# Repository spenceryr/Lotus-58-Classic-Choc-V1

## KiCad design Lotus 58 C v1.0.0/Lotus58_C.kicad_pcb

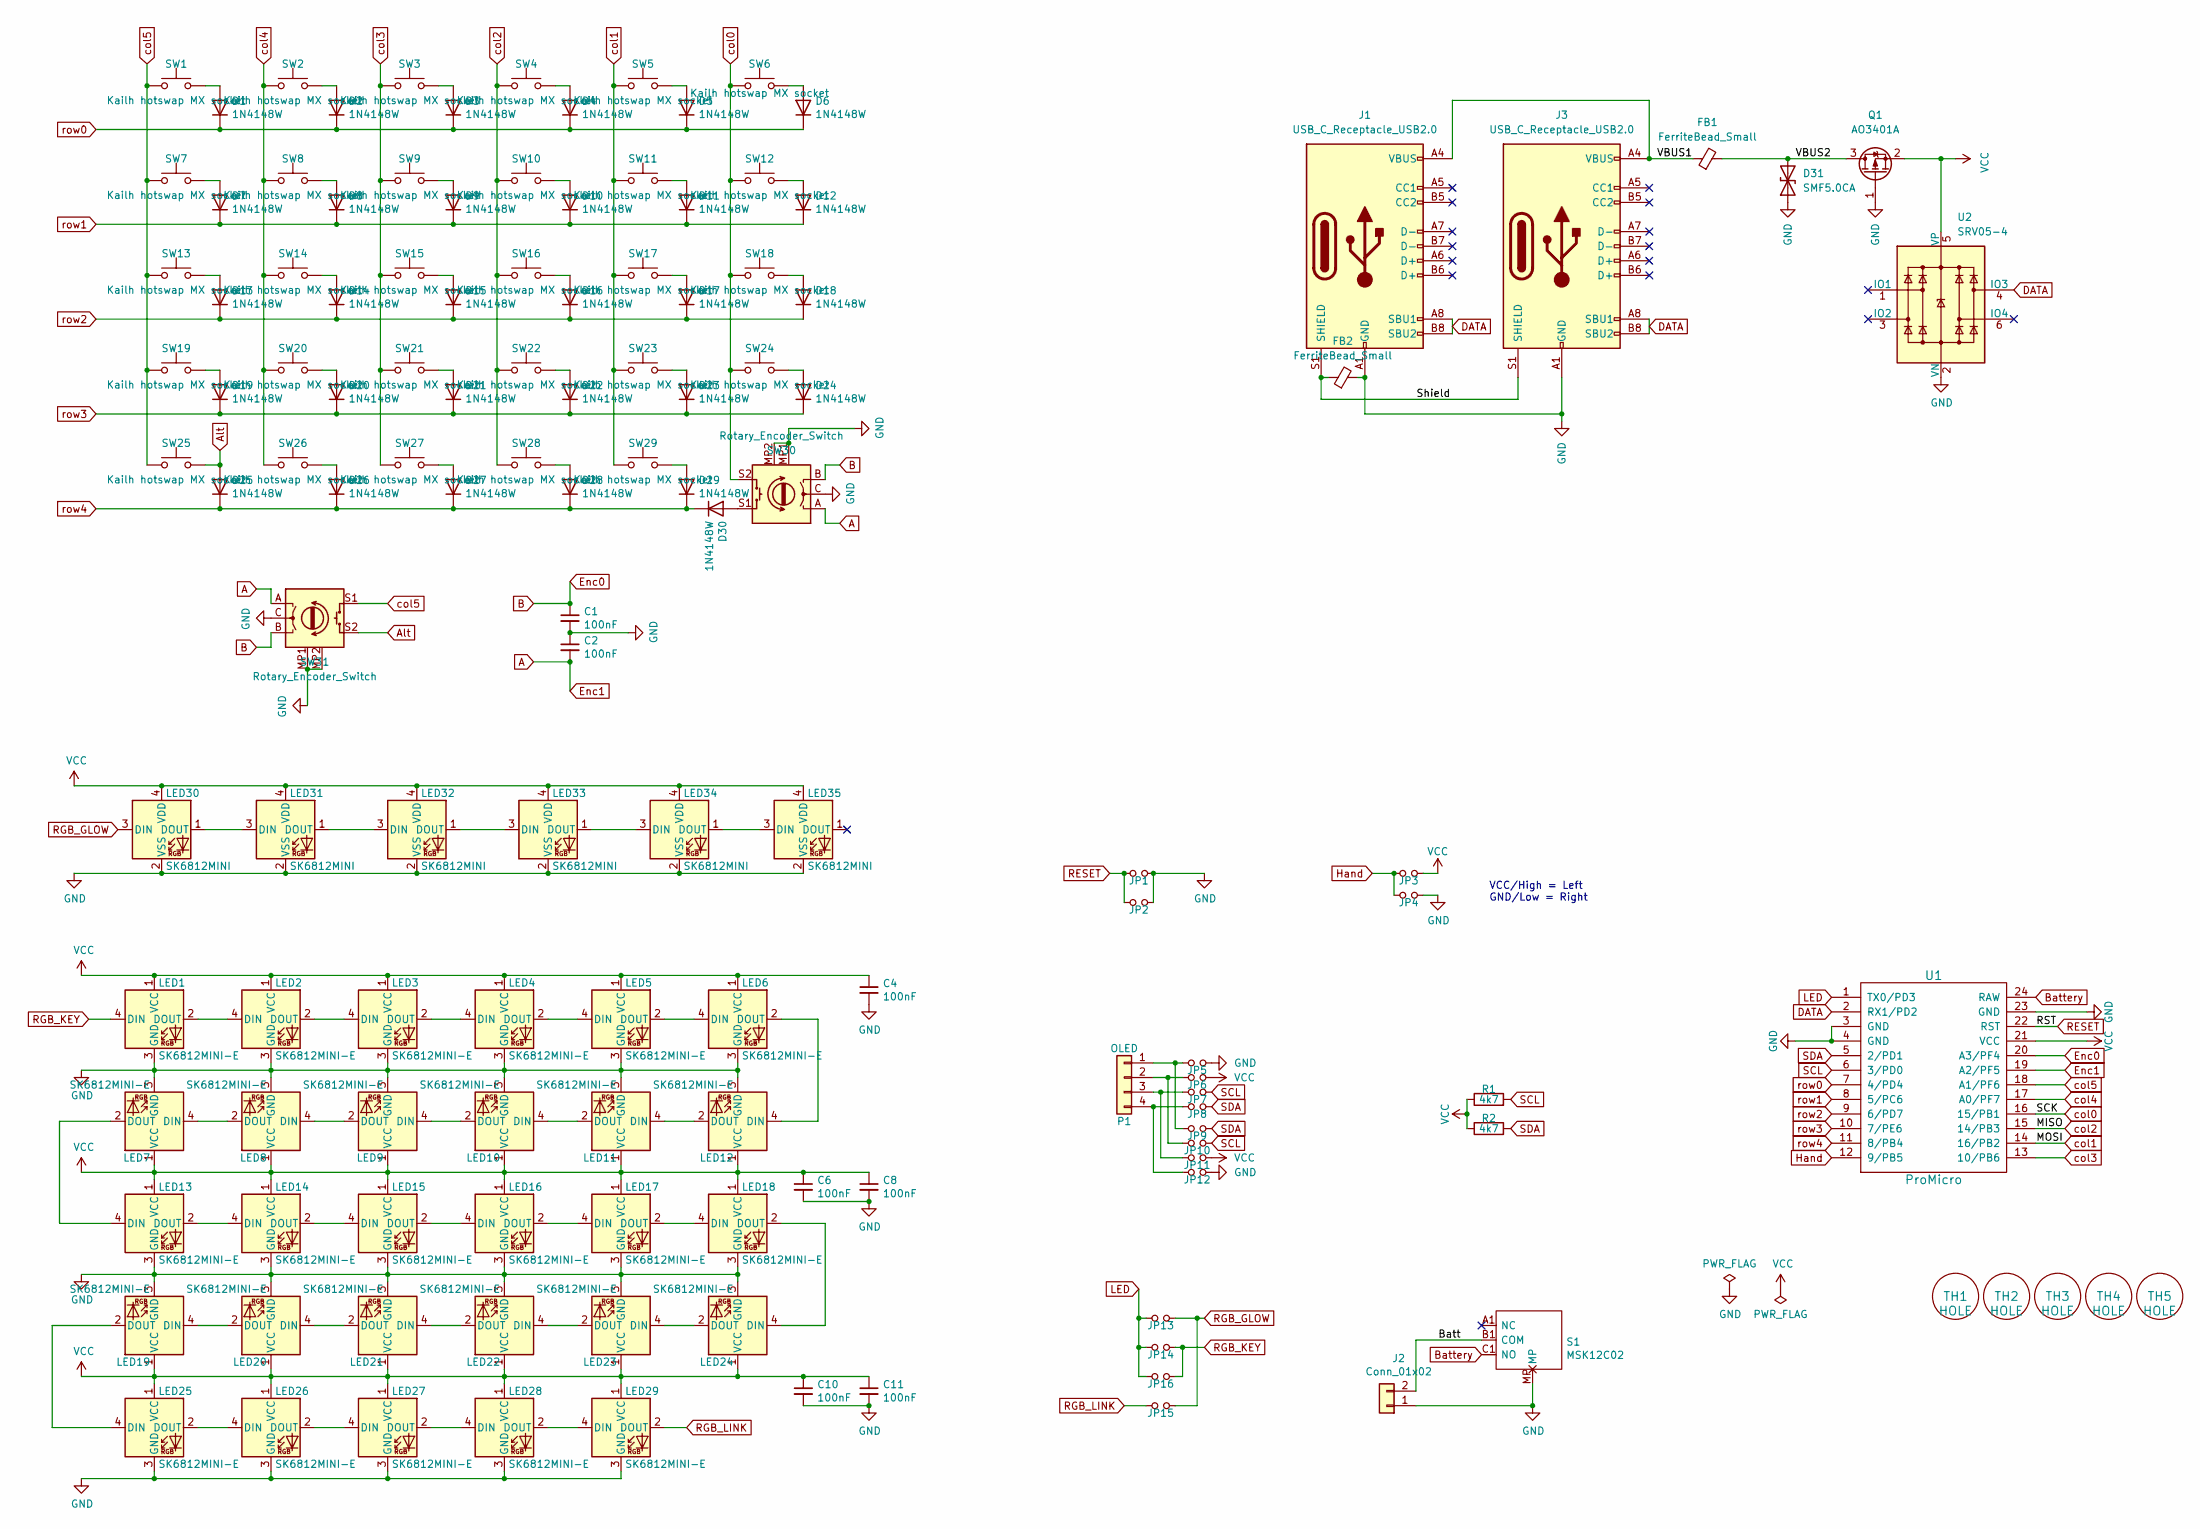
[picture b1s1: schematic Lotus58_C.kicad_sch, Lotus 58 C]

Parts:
C1, C2, C4, C6, C8, C10, C11: 100nF; C_0603_1608Metric_Pad1.08x0.95mm_HandSolder
D1, D2, D3, D4, D5, D6, D7, D8, D9, D10, D11, D12, D13, D14, D15, D16, D17, D18, D19, D20, D21, D22, D23, D24, D25, D26, D27, D28, D29, D30: 1N4148W; D_SOD-123
D31: SMF5.0CA; D_SOD-123
FB1, FB2: FerriteBead_Small; C_0805_2012Metric_Pad1.18x1.45mm_HandSolder
J1, J3: USB_C_Receptacle_USB2.0; HRO_TYPE-C-31-M-12
J2: Conn_01x02; PinHeader_1x02_P2.54mm_Vertical
JP1, JP2: RESET; Jumper_Mini
JP3: LEFT; Jumper_Mini
JP4: RIGHT; Jumper_Mini
JP5, JP6, JP7, JP8, JP9, JP10, JP11, JP12: Jumper_NO_Small; Jumper_Mini
JP13, JP14, JP15, JP16: FULL; Jumper_Mini
LED1, LED2, LED3, LED4, LED5, LED6, LED7, LED8, LED9, LED10, LED11, LED12, LED13, LED14, LED15, LED16, LED17, LED18, LED19, LED20, LED21, LED22, LED23, LED24, LED25, LED26, LED27, LED28, LED29: SK6812MINI-E; MX_SK6812MINI-E_REVERSIBLE
LED30, LED31, LED32, LED33, LED34, LED35: SK6812MINI; LED_SK6812MINI_PLCC4_3.5x3.5mm_P1.75mm
P1: OLED; SSD1306-0.91-OLED-4pin-128x32
Q1: AO3401A; SOT-23
R1, R2: 4k7; R_0603_1608Metric_Pad0.98x0.95mm_HandSolder
S1: MSK12C02; Manufacturer_Part_Number MSK12C02
SW1, SW2, SW3, SW4, SW5, SW6, SW7, SW8, SW9, SW10, SW11, SW12, SW13, SW14, SW15, SW16, SW17, SW18, SW19, SW20, SW21, SW22, SW23, SW24, SW25, SW26, SW27, SW28, SW29: Kailh hotswap MX socket; Kailh_socket_MX_reversible_RGB
SW30: Rotary_Encoder_Switch; RotaryEncoder_Alps_EC11E-Switch_Vertical_H20_special
SW31: Rotary_Encoder_Switch; RotaryEncoder_Alps_EC11E-Switch_Special
TH1, TH2, TH3, TH4, TH5: HOLE; MountingHole_3.7mm
U1: ProMicro; ProMicro_Reversible
U2: SRV05-4; SOT-23-6

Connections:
/Batt: J2.2, S1.B1 (COM)
/Shield: FB2.1, J1.S1 (SHIELD), J3.S1 (SHIELD)
/VBUS1: FB1.1, J1.A4 (VBUS), J1.A9 (VBUS), J1.B4 (VBUS), J1.B9 (VBUS), J3.A4 (VBUS), J3.A9 (VBUS), J3.B4 (VBUS), J3.B9 (VBUS)
/VBUS2: D31.2 (A2), FB1.2, Q1.3 (D)
A: C2.2, SW30.A, SW31.A, U1.19 (A2/PF5)
Alt: D25.2 (A), SW25.2, SW31.S2
B: C1.1, SW30.B, SW31.B, U1.20 (A3/PF4)
Battery: S1.C1 (NO), U1.24 (RAW)
DATA: J1.A8 (SBU1), J1.B8 (SBU2), J3.A8 (SBU1), J3.B8 (SBU2), U1.2 (RX1/PD2), U2.4 (IO3)
GND: C1.2, C2.1, C4.2, C6.2, C8.2, C10.2, C11.2, D31.1 (A1), FB2.2, J1.A1 (GND), J1.A12 (GND), J1.B1 (GND), J1.B12 (GND), J2.1, J3.A1 (GND), J3.A12 (GND), J3.B1 (GND), J3.B12 (GND), JP1.2, JP2.2, JP4.2, JP5.2, JP12.2, LED1.3 (GND), LED2.3 (GND), LED3.3 (GND), LED4.3 (GND), LED5.3 (GND), LED6.3 (GND), LED7.3 (GND), LED8.3 (GND), LED9.3 (GND), LED10.3 (GND), LED11.3 (GND), LED12.3 (GND), LED13.3 (GND), LED14.3 (GND), LED15.3 (GND), LED16.3 (GND), LED17.3 (GND), LED18.3 (GND), LED19.3 (GND), LED20.3 (GND), LED21.3 (GND), LED22.3 (GND), LED23.3 (GND), LED24.3 (GND), LED25.3 (GND), LED26.3 (GND), LED27.3 (GND), LED28.3 (GND), LED29.3 (GND), LED30.2 (VSS), LED31.2 (VSS), LED32.2 (VSS), LED33.2 (VSS), LED34.2 (VSS), LED35.2 (VSS), Q1.1 (G), S1.MP, SW30.C, SW30.MP1 (GND), SW30.MP2 (GND), SW31.C, SW31.MP1 (GND), SW31.MP2 (GND), U1.3 (GND), U1.4 (GND), U1.23 (GND), U2.2 (VN)
Hand: JP3.1, JP4.1, U1.12 (9/PB5)
LED: JP13.1, JP14.1, JP16.1, U1.1 (TX0/PD3)
unnamed: D1.2 (A), SW1.2
unnamed: D2.2 (A), SW2.2
unnamed: D3.2 (A), SW3.2
unnamed: D4.2 (A), SW4.2
unnamed: D5.2 (A), SW5.2
unnamed: D6.2 (A), SW6.2
unnamed: D7.2 (A), SW7.2
unnamed: D8.2 (A), SW8.2
unnamed: D9.2 (A), SW9.2
unnamed: D10.2 (A), SW10.2
unnamed: D11.2 (A), SW11.2
unnamed: D12.2 (A), SW12.2
unnamed: D13.2 (A), SW13.2
unnamed: D14.2 (A), SW14.2
unnamed: D15.2 (A), SW15.2
unnamed: D16.2 (A), SW16.2
unnamed: D17.2 (A), SW17.2
unnamed: D18.2 (A), SW18.2
unnamed: D19.2 (A), SW19.2
unnamed: D20.2 (A), SW20.2
unnamed: D21.2 (A), SW21.2
unnamed: D22.2 (A), SW22.2
unnamed: D23.2 (A), SW23.2
unnamed: D24.2 (A), SW24.2
unnamed: D26.2 (A), SW26.2
unnamed: D27.2 (A), SW27.2
unnamed: D28.2 (A), SW28.2
unnamed: D29.2 (A), SW29.2
unnamed: D30.2 (A), SW30.S1
unnamed: JP5.1, JP9.1, P1.1
unnamed: JP6.1, JP10.1, P1.2
unnamed: JP7.1, JP11.1, P1.3
unnamed: JP8.1, JP12.1, P1.4
unnamed: LED1.2 (DOUT), LED2.4 (DIN)
unnamed: LED2.2 (DOUT), LED3.4 (DIN)
unnamed: LED3.2 (DOUT), LED4.4 (DIN)
unnamed: LED4.2 (DOUT), LED5.4 (DIN)
unnamed: LED5.2 (DOUT), LED6.4 (DIN)
unnamed: LED7.4 (DIN), LED8.2 (DOUT)
unnamed: LED8.4 (DIN), LED9.2 (DOUT)
unnamed: LED9.4 (DIN), LED10.2 (DOUT)
unnamed: LED10.4 (DIN), LED11.2 (DOUT)
unnamed: LED11.4 (DIN), LED12.2 (DOUT)
unnamed: LED6.2 (DOUT), LED12.4 (DIN)
unnamed: LED13.2 (DOUT), LED14.4 (DIN)
unnamed: LED7.2 (DOUT), LED13.4 (DIN)
unnamed: LED14.2 (DOUT), LED15.4 (DIN)
unnamed: LED15.2 (DOUT), LED16.4 (DIN)
unnamed: LED16.2 (DOUT), LED17.4 (DIN)
unnamed: LED17.2 (DOUT), LED18.4 (DIN)
unnamed: LED18.2 (DOUT), LED24.4 (DIN)
unnamed: LED19.2 (DOUT), LED25.4 (DIN)
unnamed: LED19.4 (DIN), LED20.2 (DOUT)
unnamed: LED20.4 (DIN), LED21.2 (DOUT)
unnamed: LED21.4 (DIN), LED22.2 (DOUT)
unnamed: LED22.4 (DIN), LED23.2 (DOUT)
unnamed: LED23.4 (DIN), LED24.2 (DOUT)
unnamed: LED25.2 (DOUT), LED26.4 (DIN)
unnamed: LED26.2 (DOUT), LED27.4 (DIN)
unnamed: LED27.2 (DOUT), LED28.4 (DIN)
unnamed: LED28.2 (DOUT), LED29.4 (DIN)
unnamed: LED30.1 (DOUT), LED31.3 (DIN)
unnamed: LED31.1 (DOUT), LED32.3 (DIN)
unnamed: LED32.1 (DOUT), LED33.3 (DIN)
unnamed: LED33.1 (DOUT), LED34.3 (DIN)
unnamed: LED34.1 (DOUT), LED35.3 (DIN)
RESET: JP1.1, JP2.1, U1.22 (RST)
RGB_GLOW: JP13.2, JP15.2, LED30.3 (DIN)
RGB_KEY: JP14.2, JP16.2, LED1.4 (DIN)
RGB_LINK: JP15.1, LED29.2 (DOUT)
SCL: JP7.2, JP10.2, R1.2, U1.6 (3/PD0)
SDA: JP8.2, JP9.2, R2.2, U1.5 (2/PD1)
VCC: C4.1, C6.1, C8.1, C10.1, C11.1, JP3.2, JP6.2, JP11.2, LED1.1 (VCC), LED2.1 (VCC), LED3.1 (VCC), LED4.1 (VCC), LED5.1 (VCC), LED6.1 (VCC), LED7.1 (VCC), LED8.1 (VCC), LED9.1 (VCC), LED10.1 (VCC), LED11.1 (VCC), LED12.1 (VCC), LED13.1 (VCC), LED14.1 (VCC), LED15.1 (VCC), LED16.1 (VCC), LED17.1 (VCC), LED18.1 (VCC), LED19.1 (VCC), LED20.1 (VCC), LED21.1 (VCC), LED22.1 (VCC), LED23.1 (VCC), LED24.1 (VCC), LED25.1 (VCC), LED26.1 (VCC), LED27.1 (VCC), LED28.1 (VCC), LED29.1 (VCC), LED30.4 (VDD), LED31.4 (VDD), LED32.4 (VDD), LED33.4 (VDD), LED34.4 (VDD), LED35.4 (VDD), Q1.2 (S), R1.1, R2.1, U1.21 (VCC), U2.5 (VP)
col0: SW6.1, SW12.1, SW18.1, SW24.1, SW30.S2, U1.16 (15/PB1)
col1: SW5.1, SW11.1, SW17.1, SW23.1, SW29.1, U1.14 (16/PB2)
col2: SW4.1, SW10.1, SW16.1, SW22.1, SW28.1, U1.15 (14/PB3)
col3: SW3.1, SW9.1, SW15.1, SW21.1, SW27.1, U1.13 (10/PB6)
col4: SW2.1, SW8.1, SW14.1, SW20.1, SW26.1, U1.17 (A0/PF7)
col5: SW1.1, SW7.1, SW13.1, SW19.1, SW25.1, SW31.S1, U1.18 (A1/PF6)
row0: D1.1 (K), D2.1 (K), D3.1 (K), D4.1 (K), D5.1 (K), D6.1 (K), U1.7 (4/PD4)
row1: D7.1 (K), D8.1 (K), D9.1 (K), D10.1 (K), D11.1 (K), D12.1 (K), U1.8 (5/PC6)
row2: D13.1 (K), D14.1 (K), D15.1 (K), D16.1 (K), D17.1 (K), D18.1 (K), U1.9 (6/PD7)
row3: D19.1 (K), D20.1 (K), D21.1 (K), D22.1 (K), D23.1 (K), D24.1 (K), U1.10 (7/PE6)
row4: D25.1 (K), D26.1 (K), D27.1 (K), D28.1 (K), D29.1 (K), D30.1 (K), U1.11 (8/PB4)

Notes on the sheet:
VCC/High = Left GND/Low = Right

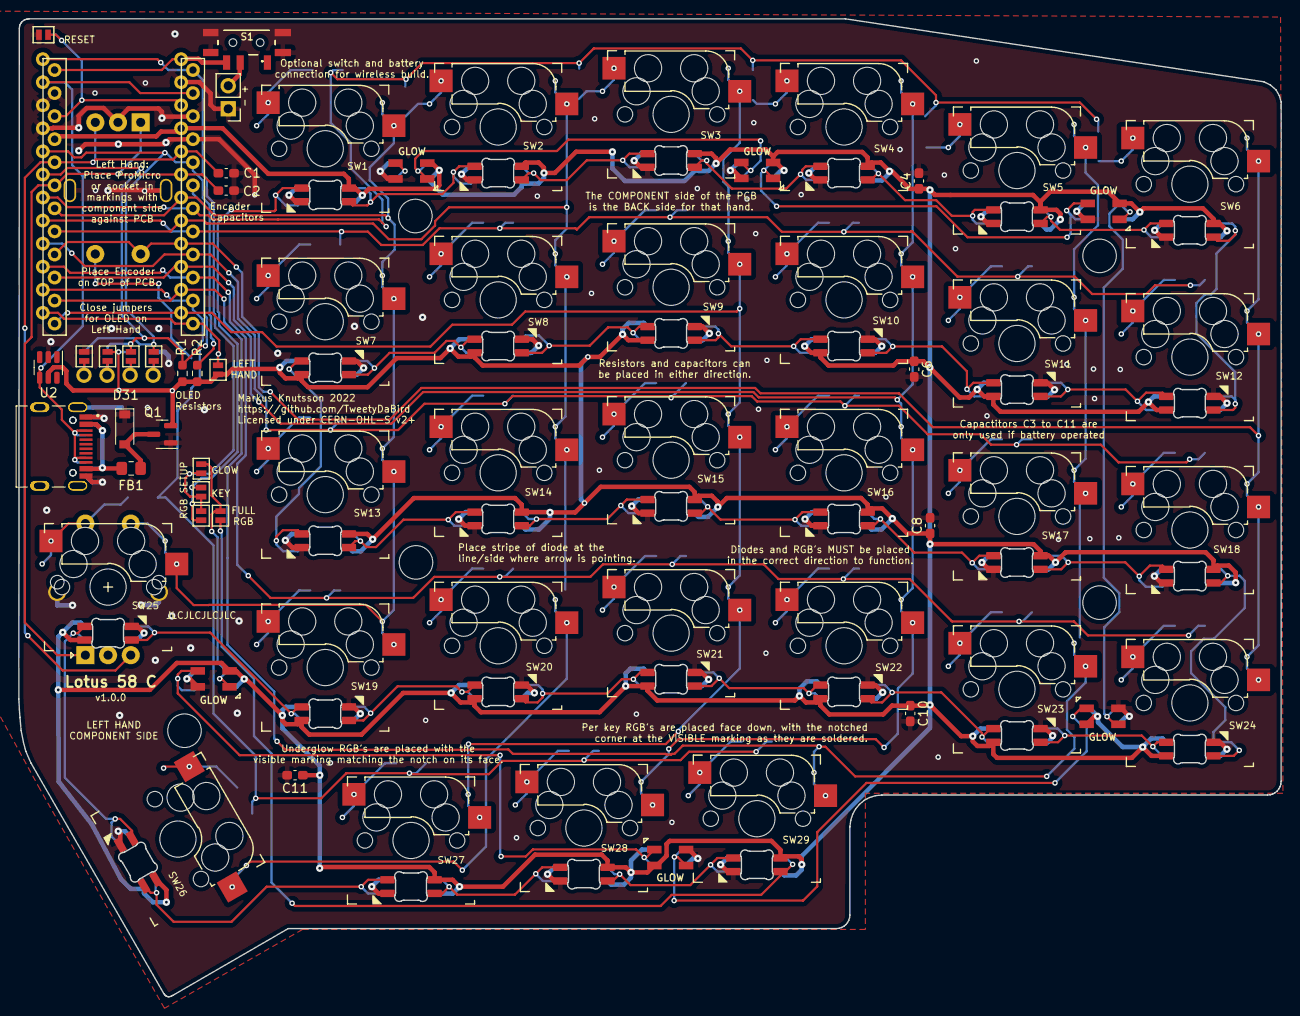
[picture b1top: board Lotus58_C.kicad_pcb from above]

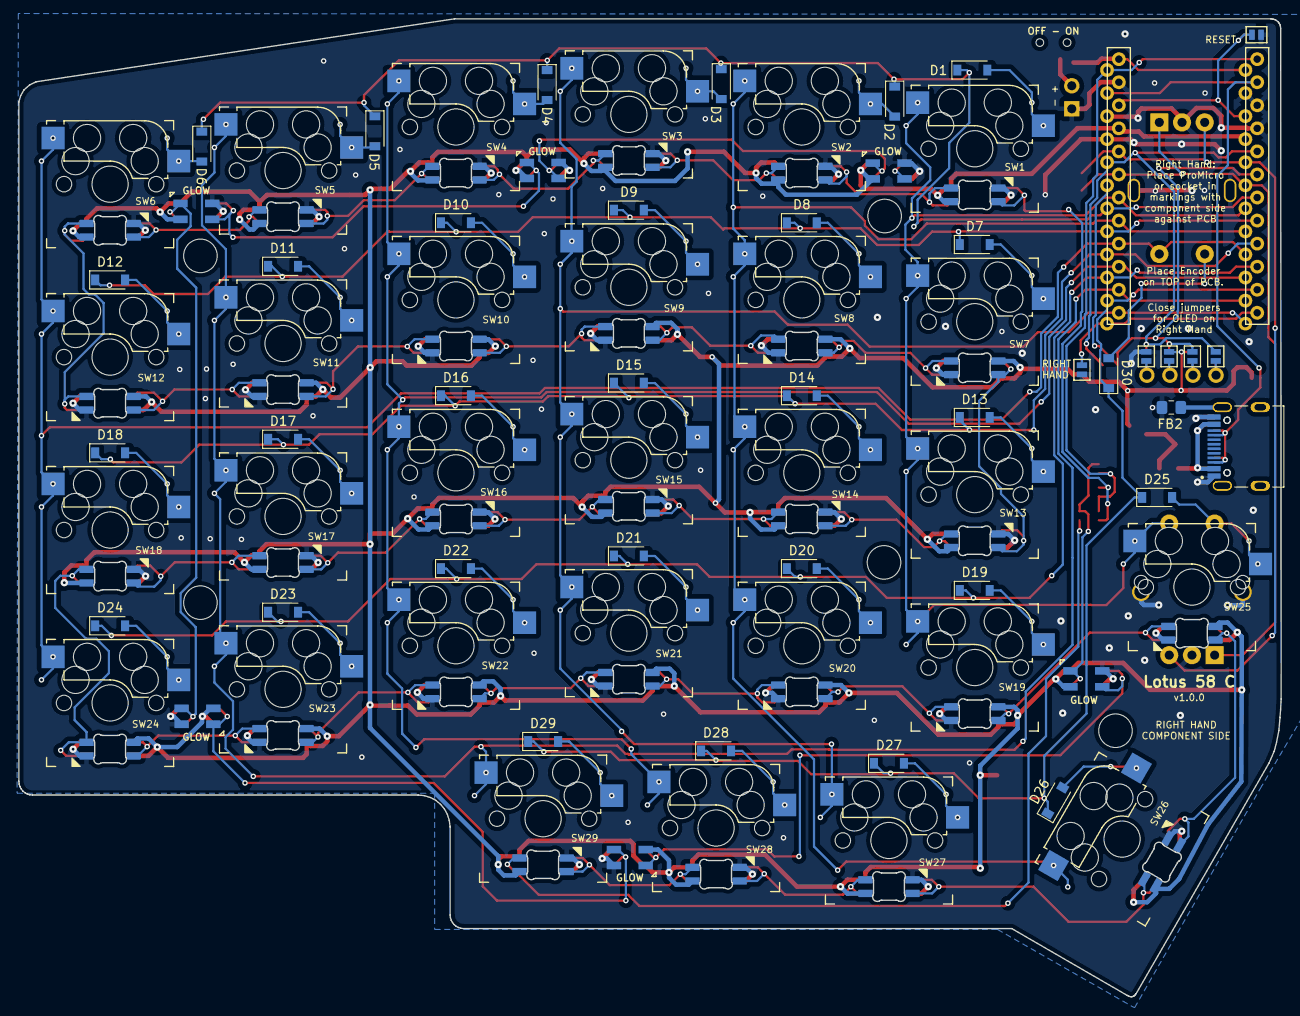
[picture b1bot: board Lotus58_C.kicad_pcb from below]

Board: 2 copper layers, 139.1 x 107.7 mm, 137 parts (39 on the bottom side), 96 nets.

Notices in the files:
Lotus 58 C v1.0.0/Lotus58_C.kicad_pcb:
Licensed under CERN-OHL-S v2 or any superseding version
